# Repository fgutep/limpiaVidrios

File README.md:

# limpiaVidrios
Limpia vidrios para materiales

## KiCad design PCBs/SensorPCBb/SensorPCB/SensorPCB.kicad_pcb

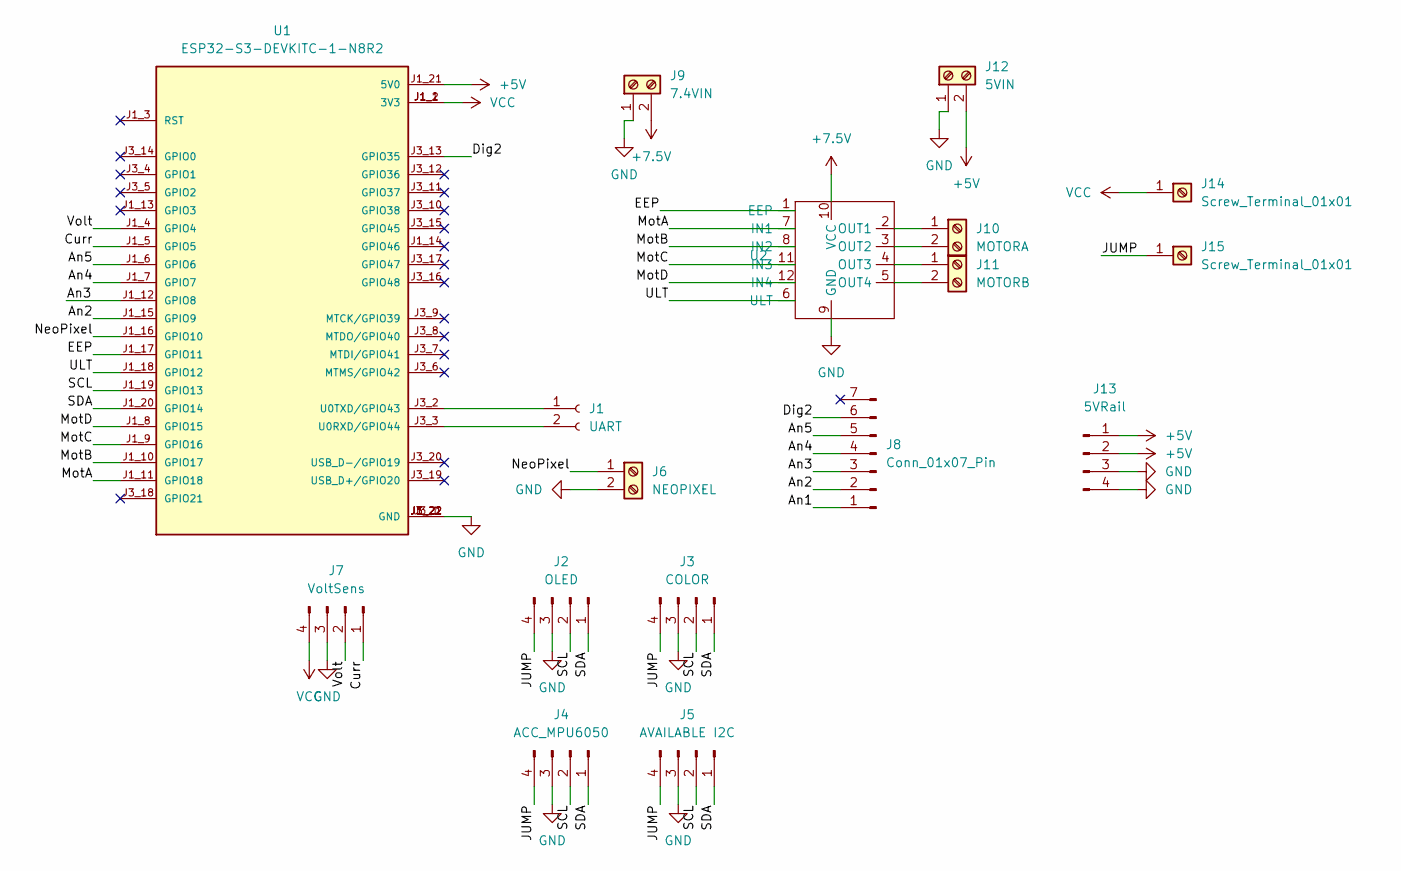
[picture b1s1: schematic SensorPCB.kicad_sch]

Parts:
J1: UART; PinHeader_1x02_P2.54mm_Vertical
J2: OLED; JST_EH_B4B-EH-A_1x04_P2.50mm_Vertical
J3: COLOR; JST_EH_B4B-EH-A_1x04_P2.50mm_Vertical
J4: ACC_MPU6050; JST_EH_B4B-EH-A_1x04_P2.50mm_Vertical
J5: AVAILABLE I2C; JST_EH_B4B-EH-A_1x04_P2.50mm_Vertical
J6: NEOPIXEL; TerminalBlock_4Ucon_1x02_P3.50mm_Vertical
J7: VoltSens; JST_EH_B4B-EH-A_1x04_P2.50mm_Vertical
J8: Conn_01x07_Pin; PinHeader_1x07_P2.54mm_Vertical
J9: 7.4VIN; TerminalBlock_4Ucon_1x02_P3.50mm_Vertical
J10: MOTORA; TerminalBlock_4Ucon_1x02_P3.50mm_Vertical
J11: MOTORB; TerminalBlock_4Ucon_1x02_P3.50mm_Vertical
J12: 5VIN; TerminalBlock_4Ucon_1x02_P3.50mm_Vertical
J13: 5VRail; PinHeader_1x04_P2.54mm_Vertical
J14, J15: Screw_Terminal_01x01; PinHeader_1x01_P2.54mm_Vertical
U1: ESP32-S3-DEVKITC-1-N8R2; PARTREV V1
U2: DRV8833

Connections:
+5V: J12.2, J13.1, J13.2, U1.J1_21 (5V0)
+7.5V: J9.2, U2.10 (VCC)
/An1: J8.1
/An2: J8.2, U1.J1_15 (GPIO9)
/An3: J8.3, U1.J1_12 (GPIO8)
/An4: J8.4, U1.J1_7 (GPIO7)
/An5: J8.5, U1.J1_6 (GPIO6)
/Curr: J7.1, U1.J1_5 (GPIO5)
/Dig2: J8.6, U1.J3_13 (GPIO35)
/EEP: U1.J1_17 (GPIO11), U2.1 (EEP)
/JUMP: J2.4, J3.4, J4.4, J5.4, J15.1
/MotA: U1.J1_11 (GPIO18), U2.7 (IN1)
/MotB: U1.J1_10 (GPIO17), U2.8 (IN2)
/MotC: U1.J1_9 (GPIO16), U2.11 (IN3)
/MotD: U1.J1_8 (GPIO15), U2.12 (IN4)
/NeoPixel: J6.1, U1.J1_16 (GPIO10)
/SCL: J2.2, J3.2, J4.2, J5.2, U1.J1_19 (GPIO13)
/SDA: J2.1, J3.1, J4.1, J5.1, U1.J1_20 (GPIO14)
/ULT: U1.J1_18 (GPIO12), U2.6 (ULT)
/Volt: J7.2, U1.J1_4 (GPIO4)
GND: J2.3, J3.3, J4.3, J5.3, J6.2, J7.3, J9.1, J12.1, J13.3, J13.4, U1.J1_22 (GND), U1.J3_1 (GND), U1.J3_21 (GND), U1.J3_22 (GND), U2.9 (GND)
unnamed: J1.1, U1.J3_2 (U0TXD/GPIO43)
unnamed: J1.2, U1.J3_3 (U0RXD/GPIO44)
unnamed: J10.1, U2.2 (OUT1)
unnamed: J10.2, U2.3 (OUT2)
unnamed: J11.1, U2.4 (OUT3)
unnamed: J11.2, U2.5 (OUT4)
VCC: J7.4, J14.1, U1.J1_1 (3V3), U1.J1_2 (3V3)

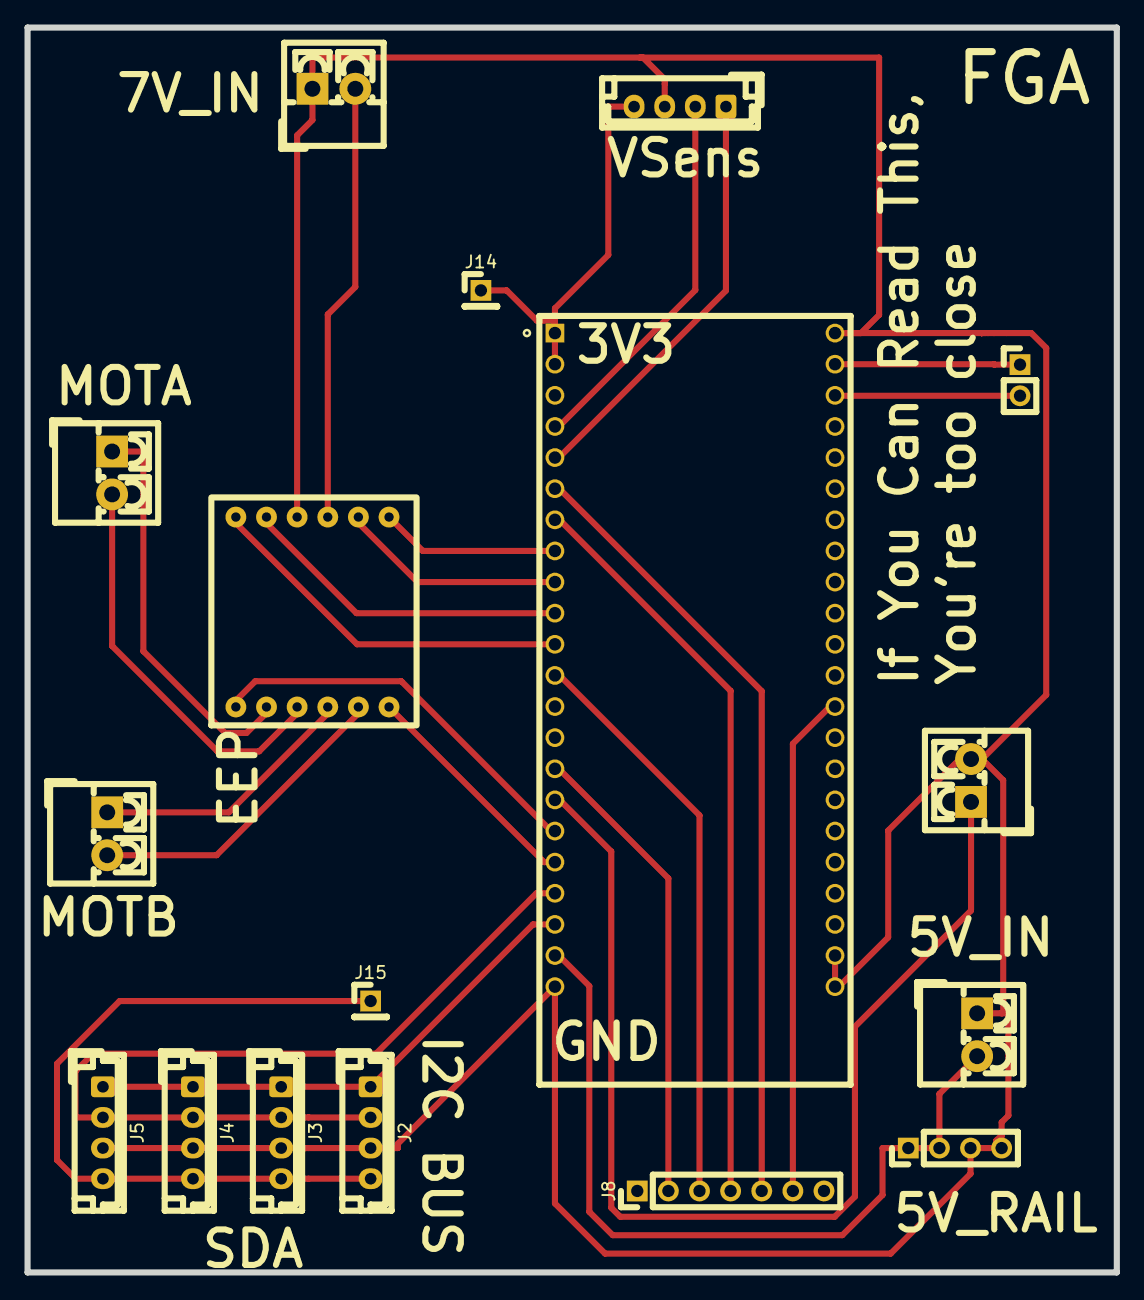
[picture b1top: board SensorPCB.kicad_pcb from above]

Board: 2 copper layers, 88.9 x 101.6 mm, 17 parts (0 on the bottom side), 27 nets.

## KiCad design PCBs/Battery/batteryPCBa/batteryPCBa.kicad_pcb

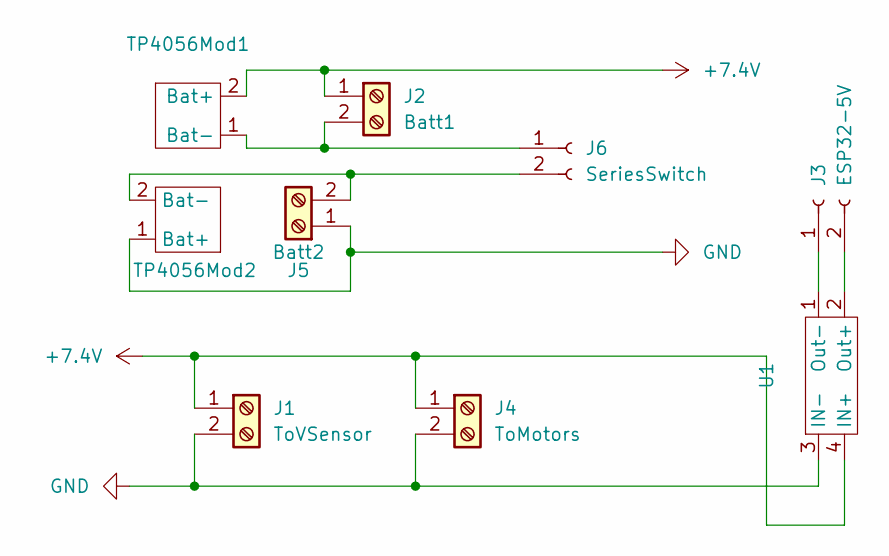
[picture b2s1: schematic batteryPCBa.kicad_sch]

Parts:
J1: ToVSensor; TerminalBlock_Xinya_XY308-2.54-2P_1x02_P2.54mm_Horizontal
J2: Batt1; TerminalBlock_Xinya_XY308-2.54-2P_1x02_P2.54mm_Horizontal
J3: ESP32-5V; JST_EH_B2B-EH-A_1x02_P2.50mm_Vertical
J4: ToMotors; TerminalBlock_Xinya_XY308-2.54-2P_1x02_P2.54mm_Horizontal
J5: Batt2; TerminalBlock_Xinya_XY308-2.54-2P_1x02_P2.54mm_Horizontal
J6: SeriesSwitch; JST_EH_B2B-EH-A_1x02_P2.50mm_Vertical
TP4056Mod1, TP4056Mod2: USBC-LiPo-ChargingModule
U1: ZX-Mini-360

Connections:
+7.4V: J1.1, J2.1, J4.1, TP4056Mod1.2 (Bat+), U1.4 (IN+)
GND: J1.2, J4.2, J5.1, TP4056Mod2.1 (Bat+), U1.3 (IN-)
unnamed: J2.2, J6.1, TP4056Mod1.1 (Bat-)
unnamed: J3.1, U1.1 (Out-)
unnamed: J3.2, U1.2 (Out+)
unnamed: J5.2, J6.2, TP4056Mod2.2 (Bat-)

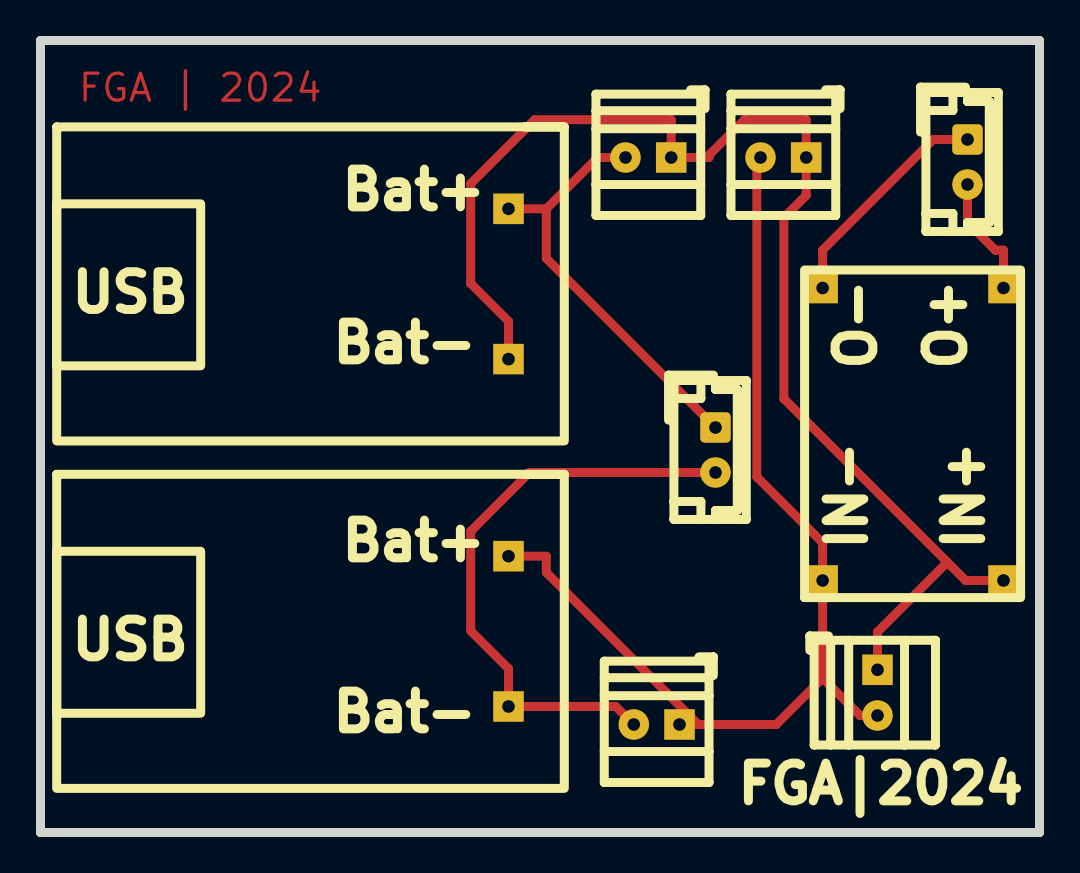
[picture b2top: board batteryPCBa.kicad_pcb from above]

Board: 2 copper layers, 55.5 x 44.0 mm, 9 parts (0 on the bottom side), 6 nets.

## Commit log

2024-11-04 Programacion
2024-11-04 Documentación programacion ESP32
2024-11-04 Delete Documentacion ProgramaciónESP32.docx
    Solo dejaré el PDF aquí en git, el docx lo guardaré en mi computador
2024-11-10 PCB Bateria V1
2024-11-20 PCBa Ultima
2024-11-23 Updates PCB
2024-11-24 Se mueve la mkada
2024-11-24 Odio los cortos
2024-11-25 Programacion ESP32, sensorica y traccion completados
2024-11-25 Dashboard
2024-12-02 Indicacion pines CleanBoard
